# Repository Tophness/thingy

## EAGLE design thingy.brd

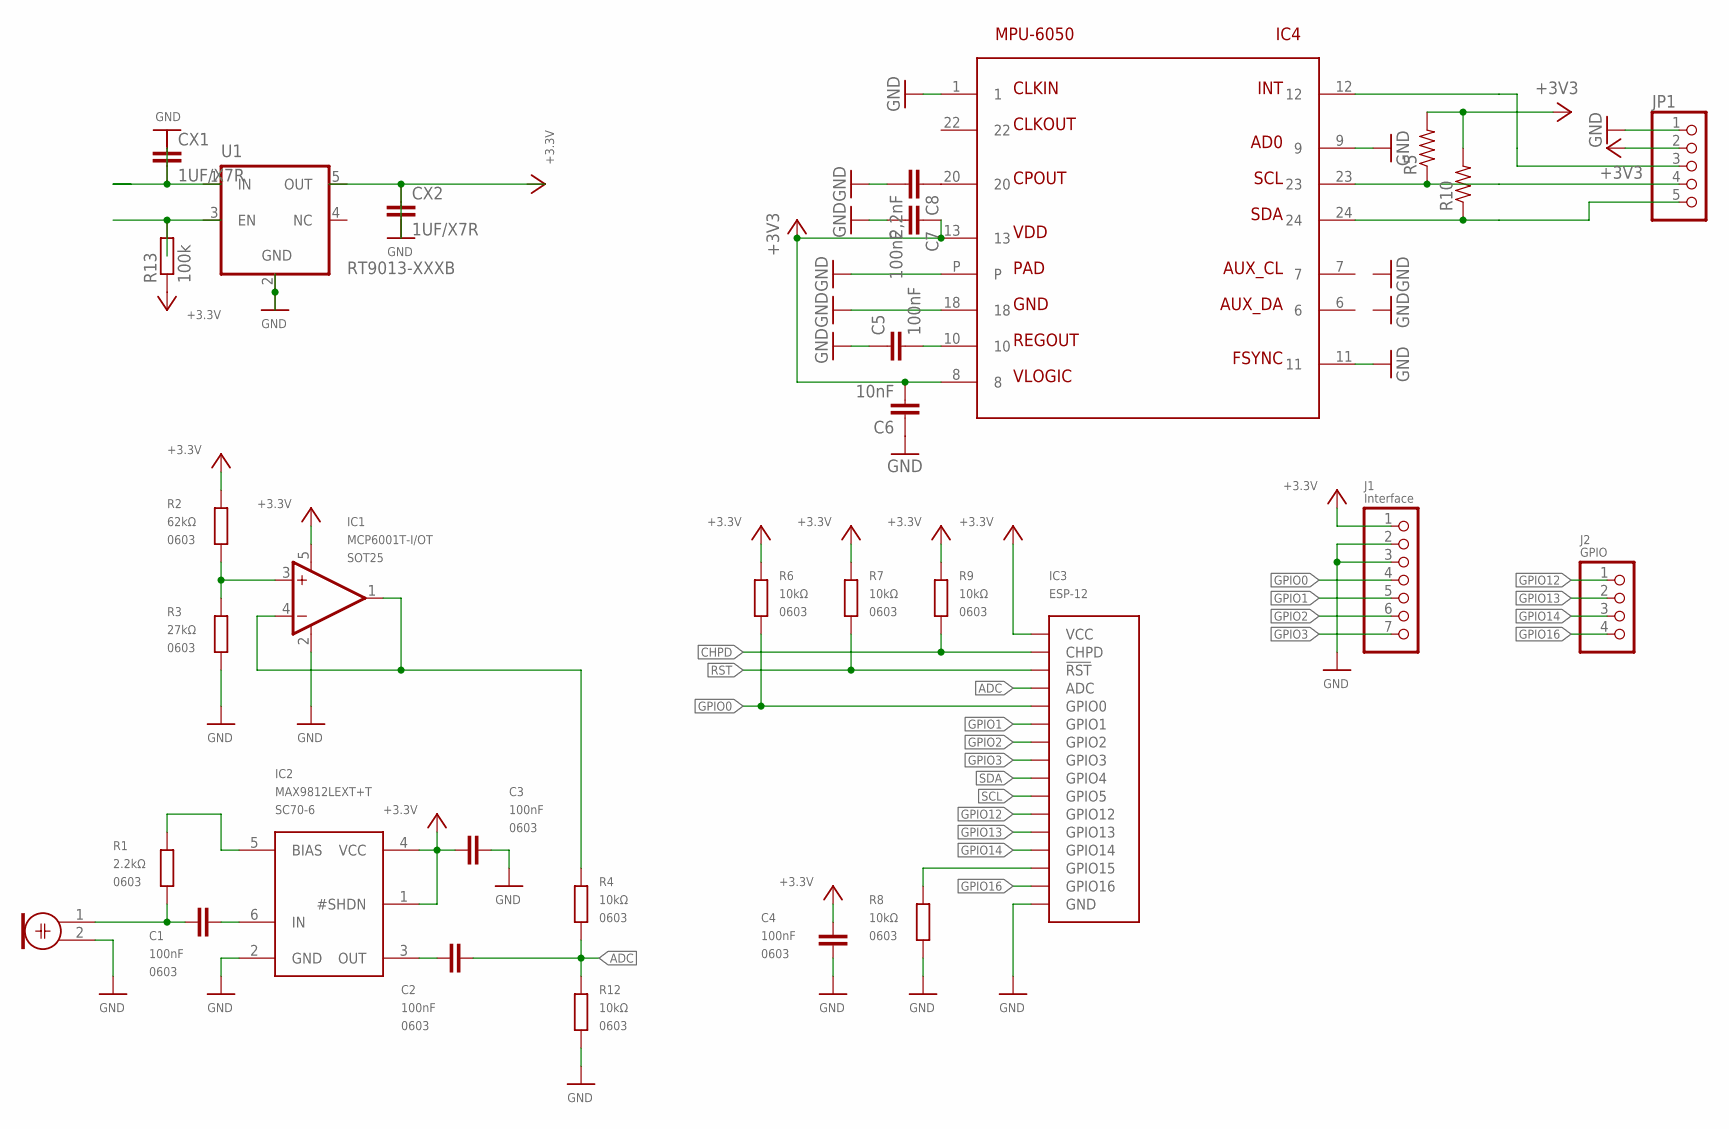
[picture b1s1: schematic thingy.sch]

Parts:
C1, C2, C3, C4: 100nF; 0603
C5, C7: 100nF; 0402-CAP
C6: 10nF; 0402-CAP
C8: 2,2nF; 0402-CAP
CX1, CX2: 1UF/X7R; XC10B5
IC1: MCP6001T-I/OT; SOT23-5
IC2: MAX9812LEXT+T; SC-70-6
IC3: ESP-12
IC4: MPU-6050; QFN24
J1: Interface; 1X07
J2: GPIO; 1X04
JP1: PINHD-1X05_2.54; 1X05
Q1: Electret Mic; WM-64PN
R1: 2.2kΩ; 0603
R2: 62kΩ; 0603
R3: 27kΩ; 0603
R4, R6, R7, R8, R9, R12: 10kΩ; 0603
R5, R10: RESISTOR0402-RES; 0402-RES
R13: 100k; R0603
U1: RT9013-XXXB; SOT23-5

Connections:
1UF/X7R: CX1.2
!RST: IC3.RST (!RST), R7.1
+3.3V: C3.1, C4.1, IC1.5 (V+), IC2.1 (#SHDN), IC2.4 (VCC), IC3.VCC, J1.1, R2.2, R6.2, R7.2, R9.2
+3V3: C6.2, C7.1, IC4.8, IC4.13, JP1.2, R5.2, R10.2
ADC: C2.2, IC3.ADC, R4.1, R12.2
CHPD: IC3.CHPD, R9.1
GND: C3.2, C4.2, C5.1, C6.1, C7.2, C8.2, IC1.2 (V-), IC2.2 (GND), IC3.GND, IC4.1, IC4.9, IC4.11, IC4.18, IC4.P, J1.2, J1.3, JP1.1, Q1.2, R3.1, R8.1, R12.1, U1.2 (GND)
GPIO0: IC3.GPIO0, J1.4, R6.1
GPIO1: IC3.GPIO1, J1.5
GPIO2: IC3.GPIO2, J1.6
GPIO3: IC3.GPIO3, J1.7
GPIO12: IC3.GPIO12, J2.1
GPIO13: IC3.GPIO13, J2.2
GPIO14: IC3.GPIO14, J2.3
GPIO16: IC3.GPIO16, J2.4
INT: IC4.12, JP1.3
unnamed: IC1.1 (OUT), IC1.4 (-IN), R4.2
unnamed: C5.2, IC4.10
unnamed: C8.1, IC4.20
unnamed: CX2.1, CX2.2
unnamed: IC3.GPIO15, R8.2
unnamed: IC1.3 (+IN), R2.1, R3.2
unnamed: C2.1, IC2.3 (OUT)
unnamed: C1.1, Q1.1, R1.1
unnamed: C1.2, IC2.6 (IN)
unnamed: IC2.5 (BIAS), R1.2
SCL: IC3.GPIO5
SCL1: IC4.23, JP1.4, R5.1
SDA: IC3.GPIO4
SDA1: IC4.24, JP1.5, R10.1

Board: 2 copper layers, 31 parts (0 on the bottom side), 27 nets, no tracks yet.

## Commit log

2017-01-19 Add files via upload
    wat is dis how 2 pley guise?
2017-01-19 Add files via upload
    This can't be right..
2017-01-20 Add files via upload
    Added the MCP6001 back in woopsie

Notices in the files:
parts and their libraries:
MAX9812: License : GNU General Public License version 2 (see bottom)
